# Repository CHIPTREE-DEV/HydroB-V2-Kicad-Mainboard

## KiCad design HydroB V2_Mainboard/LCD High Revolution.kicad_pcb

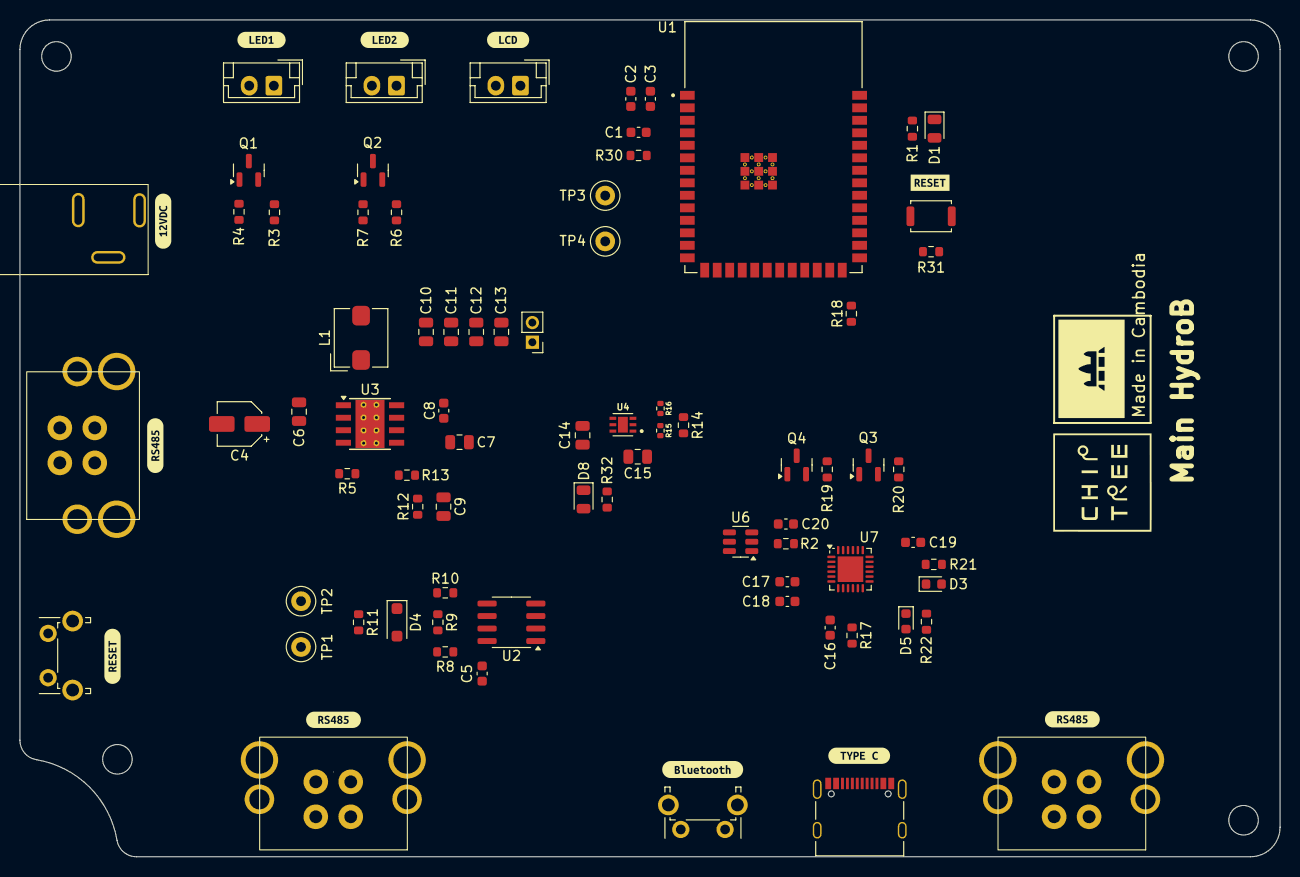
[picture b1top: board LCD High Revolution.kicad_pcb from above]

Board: 2 copper layers, 128.0 x 85.0 mm, 88 parts (0 on the bottom side), 49 nets, no tracks yet.

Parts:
C1, C5, C18, C20: 0.1uF; C_0603_1608Metric
C2: 10uF; C_0603_1608Metric
C3: 100nF; C_0603_1608Metric
C4: 10uF; CP_Elec_4x3
C6: 220nF; C_0805_2012Metric
C7, C14, C15: 1uF; C_0805_2012Metric
C8: 100NF; C_0603_1608Metric
C9: c; C_0805_2012Metric
C10, C11, C12, C13: 22uF; C_0805_2012Metric
C16, C17, C19: 1uF; C_0603_1608Metric
D1, D8: LED_Small; LED_0805_2012Metric
D3, D5: LEDR; LED_0603_1608Metric
D4: D_TVS; D_SOD-123F
J1: Conn_01x02_Pin; Modbus
J2, J4: Conn_01x02_Pin; JST_EH_B2B-EH-A_1x02_P2.50mm_Vertical
J3, J9: SENSOR; Modbus
J6: 12V; DC conn
J7: Conn_01x02_Pin; PinHeader_1x02_P2.00mm_Vertical
J8: LCD; JST_EH_B2B-EH-A_1x02_P2.50mm_Vertical
J10: USB_C_2.0; USB_C_Receptacle_Palconn_UTC16-G
L1: 2.2uH; L_Bourns_SRP5030T
Q1, Q2: S8050; SOT-23
Q3, Q4: 1P; SOT-23
R1, R17, R21, R22, R32: 1k; R_0603_1608Metric
R2: 330; R_0603_1608Metric
R3, R6: Variable Resistor; R_0603_1608Metric
R4, R7, R14: 10K; R_0603_1608Metric
R5, R12: 100k; R_0603_1608Metric
R8, R10: 2.1k; R_0603_1608Metric
R9: 124; R_0603_1608Metric
R11: 120; R_0603_1608Metric
R13: 24.9k; R_0603_1608Metric
R15: 1.96M; R_0402_1005Metric
R16: 1.18M; R_0402_1005Metric
R18, R19, R20, R30, R31: 10k; R_0603_1608Metric
SW1, SW3: SW_Push; SW_Tactile_SPST_Angled_PTS645Vx39-2LFS
SW2: SW_Push; SW_Push_SPST_NO_Alps_SKRK
TP1, TP2, TP3, TP4: TestPoint; TestPoint_Loop_D1.80mm_Drill1.0mm_Beaded
U1: ESP32-S3-WROOM-1-N16R2; XCVR_ESP32-S3-WROOM-1-N16R2
U2: SN65HVD72DR; SOIC-8_3.9x4.9mm_P1.27mm
U3: LMR33620ADDA; Texas_HSOP-8-1EP_3.9x4.9mm_P1.27mm_ThermalVias
U4: TPS7A2633DRVR; SON65P200X200X80-7N
U6: SRV05-4; SOT-23-6
U7: CP2104; QFN-24-1EP_4x4mm_P0.5mm_EP2.6x2.6mm
kibuzzard-66F384BF: G***; kibuzzard-66F384BF
kibuzzard-66F384E4: G***; kibuzzard-66F384E4
kibuzzard-66F384FE: G***; kibuzzard-66F384FE
kibuzzard-66F769D4: G***; kibuzzard-66F769D4
kibuzzard-66F3845E: G***; kibuzzard-66F3845E
kibuzzard-66F38482, kibuzzard-66F38482#2, kibuzzard-66F38482#3: G***; kibuzzard-66F38482
kibuzzard-66F38519: G***; kibuzzard-66F38519
kibuzzard-67033E7E: G***; kibuzzard-67033E7E
kibuzzard-67033E48: G***; kibuzzard-67033E48

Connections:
+3.3V: C2.2, C3.2, C5.1, C15.1, R3.1, R6.1, R8.2, R14.2, R15.1, R18.1, R30.1, R31.1, R32.1, U1.2 (3V3), U2.8 (VCC), U4.1 (OUT)
+12V: C4.1, C6.1, J3.4, J6.1, J9.4, U3.2 (VIN), U3.3 (EN)
/Mainboard/LED/LED1: R4.1, U1.25 (IO48)
/Mainboard/LED/LED2: R7.2, U1.18 (IO10)
/Mainboard/LED/RXD: J8.1, U1.7 (IO7)
/Mainboard/LED/TXD: J8.2, U1.12 (IO8)
/Mainboard/MCU/BOOT: Q4.3 (C), R31.2, SW2.2, U1.27 (IO0)
/Mainboard/MCU/EN_RS485: U1.9 (IO16), U2.2 (~RE), U2.3 (DE)
/Mainboard/MCU/RESET: C1.1, Q3.3 (C), R30.2, SW1.2, U1.3 (EN)
/Mainboard/MCU/RS485_RX: TP4.1, U1.11 (IO18), U2.4 (D)
/Mainboard/MCU/RS485_TX: TP3.1, U1.10 (IO17), U2.1 (R)
/Mainboard/MCU/UART_RX: U1.37 (TXD0), U7.20 (RXD)
/Mainboard/MCU/UART_TX: U1.36 (RXD0), U7.21 (TXD)
/Mainboard/POWER SUPPLY /SW: C8.2, L1.1, U3.8 (SW)
/Mainboard/POWER SUPPLY /SW_OUT: C9.1, C10.1, C11.1, C12.1, C13.1, J7.2, L1.2, R12.2
/Mainboard/UART/USB_D+: J10.A6 (D+), J10.B6 (D+), U6.1 (IO1), U7.3 (D+)
/Mainboard/UART/USB_D-: J10.A7 (D-), J10.B7 (D-), U6.3 (IO2), U7.4 (D-)
/Mainboard/UART/VIO: C17.2, C18.2, R17.2, R21.2, R22.2, U7.5 (VIO), U7.6 (VDD)
/Mainboard/UART/~DTR: Q4.2 (E), R19.1, U7.23 (~DTR)
/Mainboard/UART/~RST: Q3.2 (E), R20.1, U7.19 (~RTS)
/Mainboard/UART/~RXT: D5.1 (K), U7.13 (RXT/GPIO.1)
/Mainboard/UART/~TXT: D3.1 (K), U7.14 (TXT/GPIO.0)
GND: C1.2, C2.1, C3.1, C4.2, C5.2, C6.2, C7.2, C10.2, C11.2, C12.2, C13.2, C14.2, C15.2, C16.1, C17.1, C18.1, C19.1, C20.2, D1.1 (K), D8.1 (K), J3.1, J6.2, J9.1, J10.A1 (GND), J10.A12 (GND), J10.B1 (GND), J10.B12 (GND), Q1.2 (E), Q2.2 (E), R2.1, R10.1, R13.1, R16.2, SW1.1, SW2.1, SW3.2, U1.1 (GND), U1.40 (GND), U1.41_1 (GND), U1.41_2 (GND), U1.41_3 (GND), U1.41_4 (GND), U1.41_5 (GND), U1.41_6 (GND), U1.41_7 (GND), U1.41_8 (GND), U1.41_9 (GND), U2.5 (GND), U3.1 (GND), U3.9 (GND), U4.5 (GND), U4.7 (EXP), U7.2 (GND), U7.25 (GND)
GNDPWR: C20.1, J10.S1 (SHIELD), R2.2, U6.2 (VN)
LED: R1.1, U1.38 (IO2)
unnamed: D1.2 (A), R1.2
unnamed: D3.2 (A), R21.1
unnamed: D4.1 (A1), J1.1, J3.3, J9.3, R9.1, R10.2, R11.1, TP2.1, U2.6 (A)
unnamed: D4.2 (A2), J1.2, J3.2, J9.2, R8.1, R9.2, R11.2, TP1.1, U2.7 (B)
unnamed: D5.2 (A), R22.1
unnamed: D8.2 (A), R32.2
unnamed: J2.1, R3.2
unnamed: J2.2, Q1.3 (C)
unnamed: J4.1, R6.2
unnamed: J4.2, Q2.3 (C)
unnamed: Q1.1 (B), R4.2
unnamed: Q2.1 (B), R7.1
unnamed: Q3.1 (B), R19.2
unnamed: Q4.1 (B), R20.2
unnamed: R18.2, SW3.1, U1.26 (IO45)
unnamed: C8.1, U3.7 (BOOT)
unnamed: C9.2, R12.1, R13.2, U3.5 (FB)
unnamed: C7.1, R5.2, U3.6 (VCC)
unnamed: R15.2, R16.1, U4.2 (NC)
unnamed: R14.1, U4.3 (PG)
unnamed: C19.2, U7.16 (VPP)
unnamed: R17.1, U7.9 (~RST)
PG: R5.1, U3.4 (PG)
VBUS: C14.1, C16.2, J7.1, J10.A4 (VBUS), J10.A9 (VBUS), J10.B4 (VBUS), J10.B9 (VBUS), U4.4 (EN), U4.6 (IN), U6.5 (VP), U7.7 (REGIN), U7.8 (VBUS)

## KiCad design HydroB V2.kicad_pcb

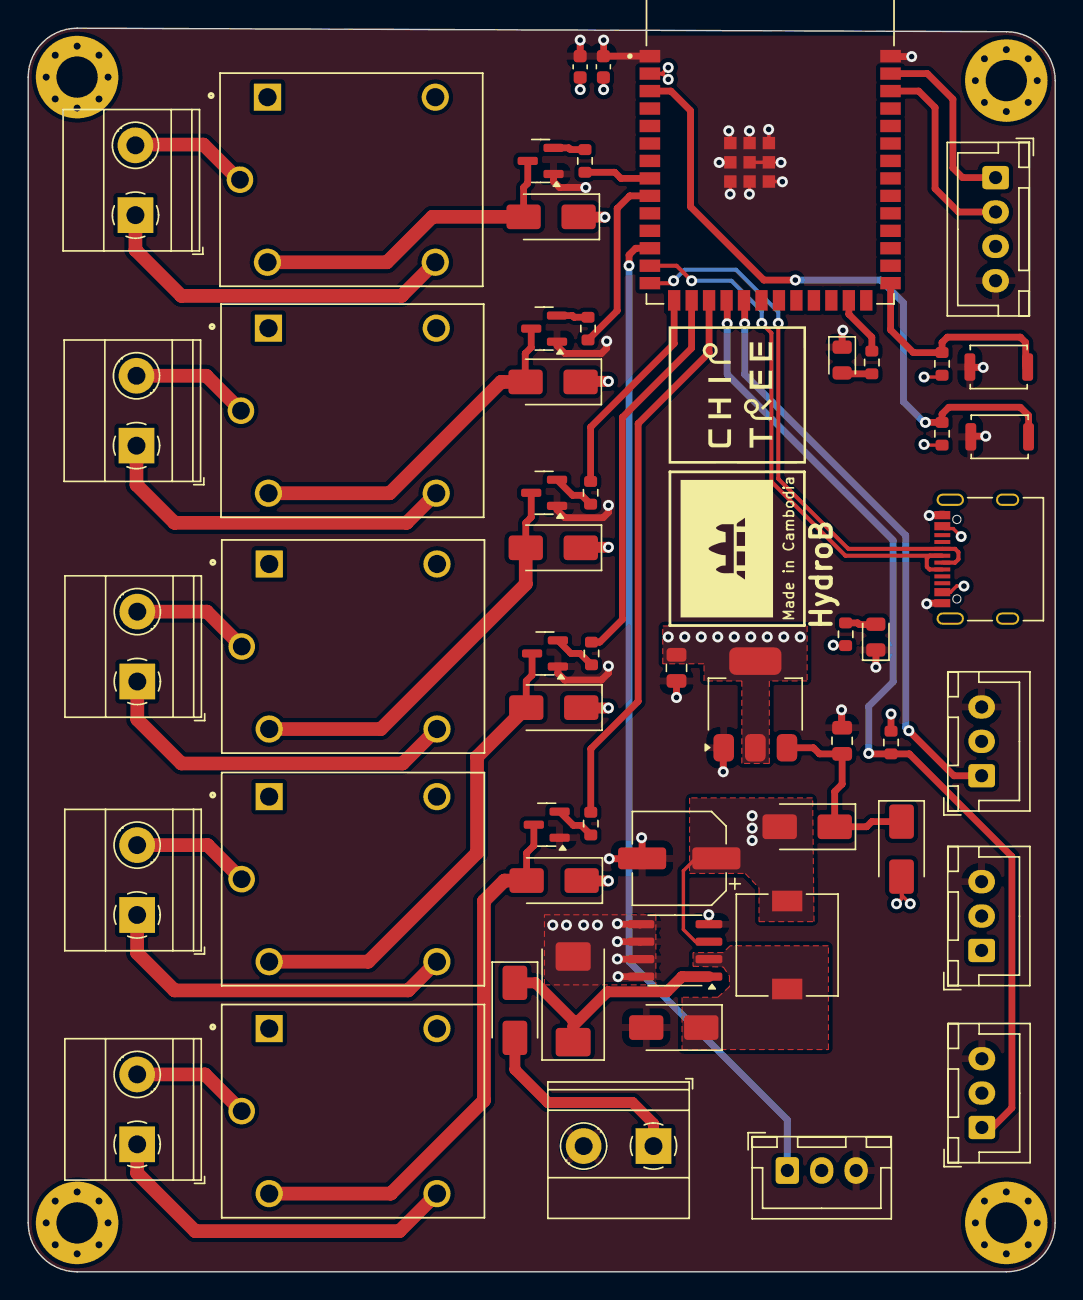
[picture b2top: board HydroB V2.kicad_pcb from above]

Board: 4 copper layers, 74.7 x 90.4 mm, 59 parts (0 on the bottom side), 45 nets.

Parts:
C4: 10uF; C_0603_1608Metric
C6: 0.1uF; C_0603_1608Metric
C8: 470uf/35V; CP_EIA-7343-30_AVX-N
C9: 180uf/35V; CP_Elec_6.3x7.7
C10, C12: 10uf; C_0805_2012Metric
D1, D20: LED_Small; LED_0805_2012Metric
D7, D8, D10, D14, D15, D16: 1N4007; D_SMA
D17: 1N5820; D_SMA
D18, D19: B120-E3; D_SMA
H5, H6, H7, H8: MountingHole; MountingHole_3mm_Pad_Via
J1: EC sensor; JST_XH_B3B-XH-A_1x03_P2.50mm_Vertical
J2, J14, J15, J16, J17, J18: Screw_Terminal_01x02; TerminalBlock_Phoenix_MKDS-1,5-2-5.08_1x02_P5.08mm_Horizont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
J20: LCD; JST_XH_B4B-XH-A_1x04_P2.50mm_Vertical
J21: DS18B20 sensor; JST_XH_B3B-XH-A_1x03_P2.50mm_Vertical
J23: PH sensor; JST_XH_B3B-XH-A_1x03_P2.50mm_Vertical
J24: Fan; JST_XH_B3B-XH-A_1x03_P2.50mm_Vertical
J26: USB_C_2.0; USB_C_Receptacle_Palconn_UTC16-G
K5, K7, K8, K9, K10: SRD-05VDC-SL-C; RELAY_SRD-05VDC-SL-C
L2: 68uH; L_7.3x7.3_H3.5
Q6, Q7, Q8, Q9, Q10: S8050; SOT-23
R1, R16: 1k; R_0603_1608Metric
R9, R11, R12, R13, R14: 470; R_0603_1608Metric
R15: 5K; R_0603_1608Metric
R17, R18: 10k; R_0603_1608Metric
SW3: K2; SW_Push_SPST_NO_Alps_SKRK
SW4: K1; SW_Push_SPST_NO_Alps_SKRK
U1: ESP32-S3-WROOM-1-N16R2; XCVR_ESP32-S3-WROOM-1-N16R2
U4: XL1509-5.0; SOIC-8_3.9x4.9mm_P1.27mm
U5: AMS1117-3.3; SOT-223-3_TabPin2

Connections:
+3.3V: C4.2, C6.2, C12.1, R16.1, R17.2, R18.2, U1.2 (3V3), U5.2 (VO)
+5V: C9.1, D7.1 (K), D8.1 (K), D10.1 (K), D14.1 (K), D15.1 (K), D18.2 (A), J1.2, J20.3, J21.2, J23.2, K5.A1, K7.A1, K8.A1, K9.A1, K10.A1, L2.2, R15.2, U4.3 (FB)
/HydroB/Block Relay1/RELAY_1: R9.1, U1.8 (IO15)
/HydroB/Block Relay1/RELAY_2: R12.1, U1.9 (IO16)
/HydroB/Block Relay1/RELAY_3: R14.1, U1.17 (IO9)
/HydroB/Block Relay1/RELAY_4: R11.1, U1.16 (IO46)
/HydroB/Block Relay1/RELAY_5: R13.1, U1.15 (IO3)
/HydroB/Block Sensor1/IO8: J23.1, U1.12 (IO8)
/HydroB/Block Sensor1/IO9: J1.1, R15.1, U1.18 (IO10)
/HydroB/Block Sensor1/IO10: J21.1, U1.19 (IO11)
/HydroB/Block Sensor1/SCL: J20.2, U1.38 (IO2)
/HydroB/Block Sensor1/SDA: J20.1, U1.39 (IO1)
/HydroB/ESP32-S3/BOOT: R18.1, SW4.2, U1.27 (IO0)
/HydroB/ESP32-S3/D+: J26.A6 (D+), J26.B6 (D+), U1.14 (IO20)
/HydroB/ESP32-S3/D-: J26.A7 (D-), J26.B7 (D-), U1.13 (IO19)
/HydroB/ESP32-S3/LED: R1.1, U1.25 (IO48)
/HydroB/ESP32-S3/RESET: R17.1, SW3.2, U1.3 (EN)
/HydroB/Power Supply/OUT: D17.1 (K), L2.1, U4.2 (OUT)
GND: C4.1, C6.1, C8.2, C9.2, C10.2, C12.2, D1.1 (K), D17.2 (A), D20.1 (K), J1.3, J2.2, J20.4, J21.3, J23.3, J24.3, J26.A1 (GND), J26.A12 (GND), J26.B1 (GND), J26.B12 (GND), Q6.1 (E), Q7.1 (E), Q8.1 (E), Q9.1 (E), Q10.1 (E), SW3.1, SW4.1, U1.1 (GND), U1.40 (GND), U1.41_1 (GND), U1.41_2 (GND), U1.41_3 (GND), U1.41_4 (GND), U1.41_5 (GND), U1.41_6 (GND), U1.41_7 (GND), U1.41_8 (GND), U1.41_9 (GND), U4.4 (~EN), U4.5 (GND), U4.6 (GND), U4.7 (GND), U4.8 (GND), U5.1 (GND)
unnamed: D1.2 (A), R1.2
unnamed: D7.2 (A), K5.A2, Q6.3 (C)
unnamed: D8.2 (A), K7.A2, Q7.3 (C)
unnamed: D10.2 (A), K8.A2, Q8.3 (C)
unnamed: D14.2 (A), K9.A2, Q9.3 (C)
unnamed: D15.2 (A), K10.A2, Q10.3 (C)
unnamed: D16.2 (A), J2.1
unnamed: C8.1, D16.1 (K), U4.1 (VIN)
unnamed: C10.1, D18.1 (K), D19.1 (K), U5.3 (VI)
unnamed: D20.2 (A), R16.2
unnamed: J14.1, K5.NO
unnamed: J14.2, K5.COM
unnamed: J15.1, K7.NO
unnamed: J15.2, K7.COM
unnamed: J16.1, K8.NO
unnamed: J16.2, K8.COM
unnamed: J17.1, K9.NO
unnamed: J17.2, K9.COM
unnamed: J18.1, K10.NO
unnamed: J18.2, K10.COM
unnamed: Q6.2 (B), R9.2
unnamed: Q7.2 (B), R11.2
unnamed: Q8.2 (B), R12.2
unnamed: Q9.2 (B), R13.2
unnamed: Q10.2 (B), R14.2
VBUS: D19.2 (A), J24.2, J26.A4 (VBUS), J26.A9 (VBUS), J26.B4 (VBUS), J26.B9 (VBUS)

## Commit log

2024-04-03 NewFolderAdded
2024-04-04 PCBFolder
2024-04-18 refactored project and fix some bugs
2024-04-18 fixed VBUS connected to +12V
2024-04-26 Update power supply and connector of sensor
2024-05-06 the schematic of sub-board updated
2024-05-10 LCD schematic of mainboard
2024-05-20 Update LCD schematic
2024-05-20 mainboard updated
2024-07-17 Schematic mainboard update
2024-09-09 Mainboard schematic update
2024-09-25 main PCB board placement
2024-10-07 PCB placement and ERC
2024-10-10 PCB placement and RUN ERC
